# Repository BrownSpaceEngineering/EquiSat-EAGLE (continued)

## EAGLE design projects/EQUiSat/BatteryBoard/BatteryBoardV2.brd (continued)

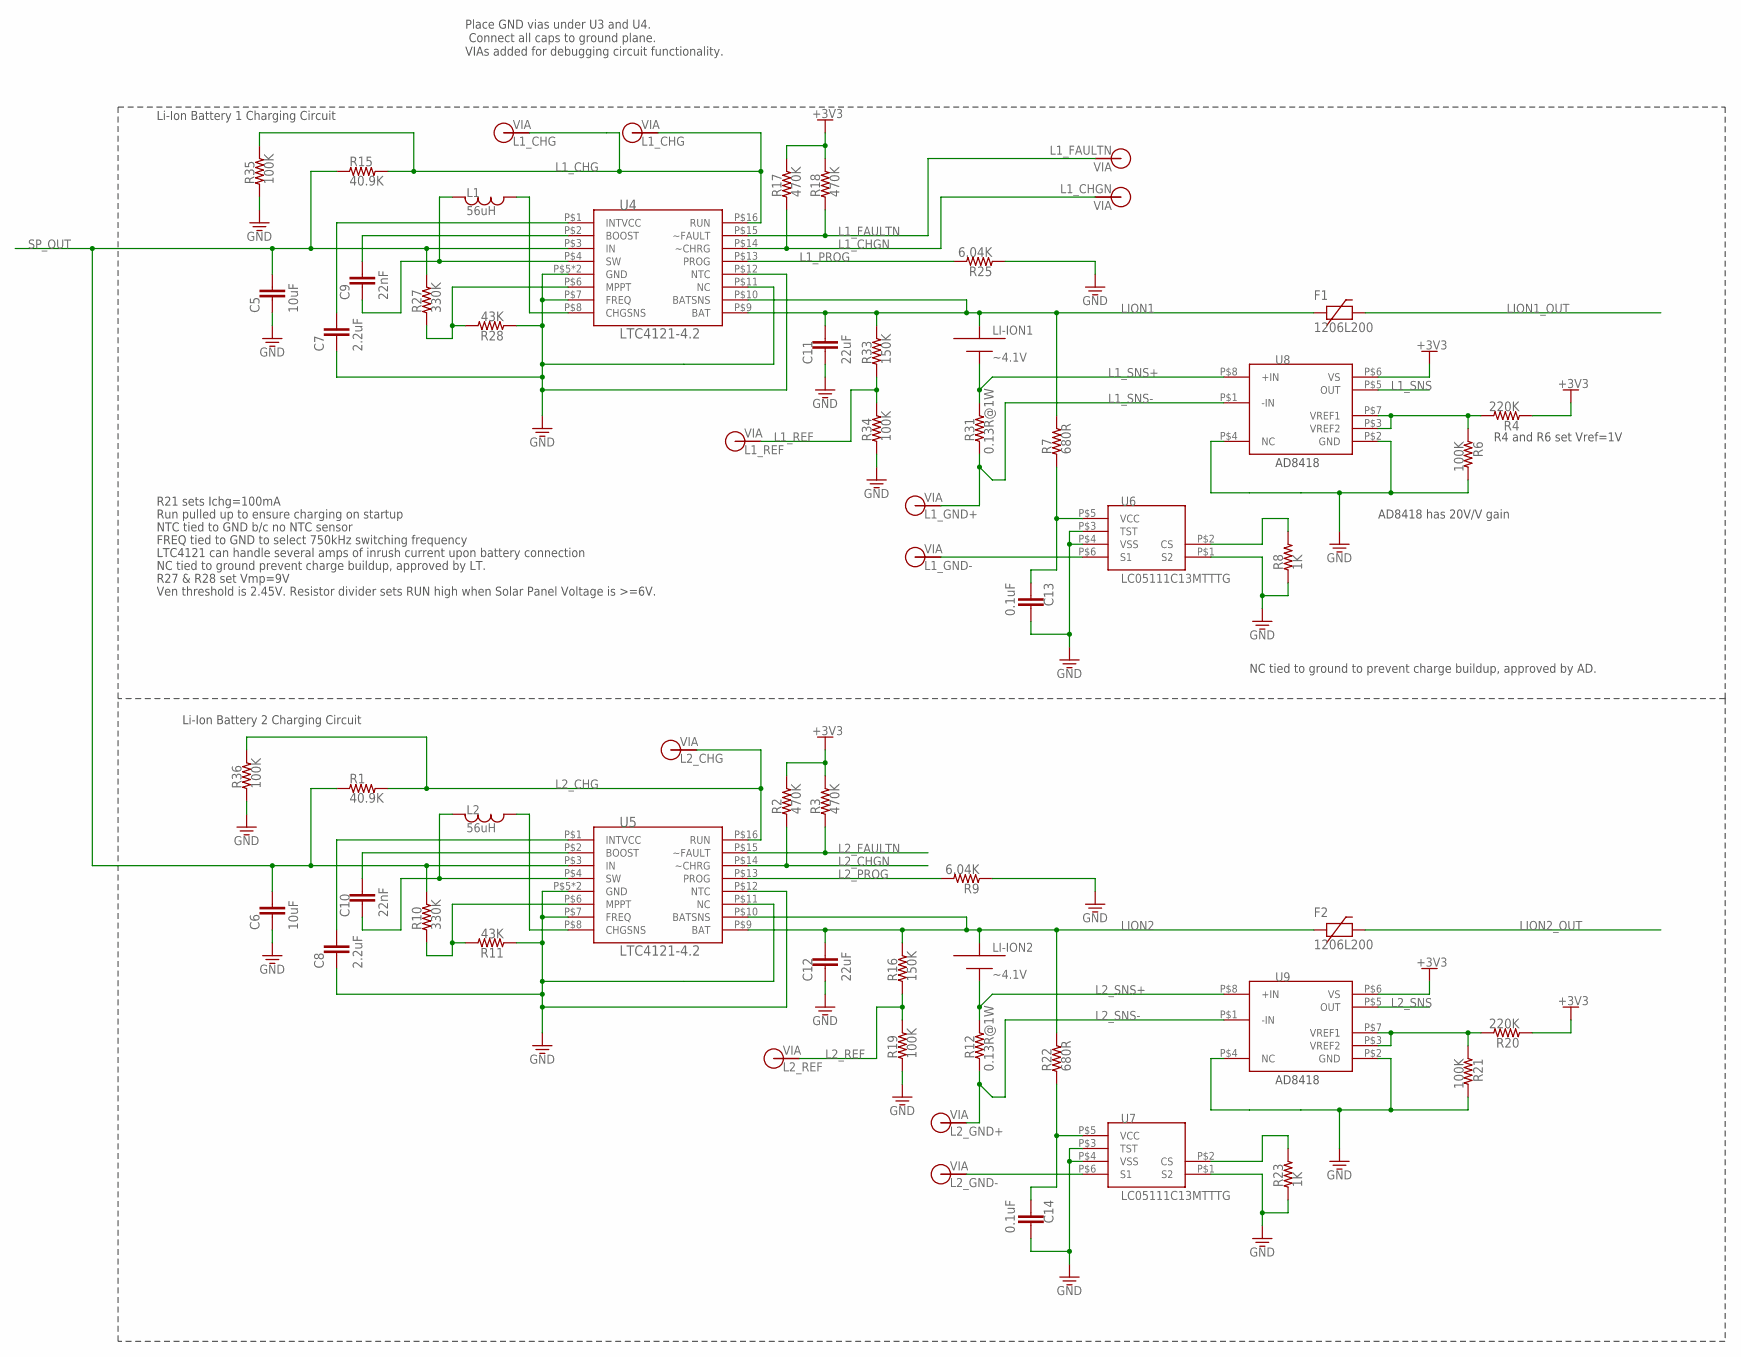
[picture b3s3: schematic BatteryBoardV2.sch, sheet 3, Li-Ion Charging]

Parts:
C5, C6: 10uF; 0805
C7, C8: 2.2uF; 0805
C9, C10: 22nF; 0805
C11, C12: 22uF; 0805
C13, C14: 0.1uF; 0805
F1, F2: 1206L200; 1206
L1, L2: 56uH; 1812
LI-ION1, LI-ION2: ~4.1V; EQUISAT-BATTERY-VA
R1, R15: 40.9K; 0805
R2, R3, R17, R18: 470K; 0805
R4, R20: 220K; 0805
R6, R19, R21, R34, R35, R36: 100K; 0805
R7, R22: 680R; 0805
R8, R23: 1K; 0805
R9, R25: 6.04K; 0805
R10, R27: 330K; 0805
R11, R28: 43K; 0805
R12, R31: 0.13R@1W; 1210
R16, R33: 150K; 0805
U4, U5: LTC4121-4.2; QFN-16-PAD
U6, U7: LC05111C13MTTTG; WDFN6
U8, U9: AD8418; MSOP-8
V20: L1_CHG; VIA-60MIL
V21: L1_REF; VIA-60MIL
V22: L1_GND+; VIA-60MIL
V23: L1_GND-; VIA-60MIL
V24: L2_GND+; VIA-60MIL
V25: L2_GND-; VIA-60MIL
V26: L1_FAULTN; VIA-60MIL-SQ
V27: L1_CHGN; VIA-60MIL-SQ
V31: L2_REF; VIA-60MIL
V33: L2_CHG; VIA-60MIL
V48: L1_CHG; VIA-60MIL-SQ

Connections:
+3V3: R2.2, R3.2, R4.1, R17.2, R18.2, R20.1, U8.P$6 (VS), U9.P$6 (VS); also elsewhere on the board
GND: C5.2, C6.2, C7.2, C8.2, C11.2, C12.2, C13.1, C14.1, R6.2, R8.1, R9.1, R11.1, R19.1, R21.2, R23.1, R25.1, R28.1, R34.1, R35.1, R36.1, U4.P$5 (GND), U4.P$7 (FREQ), U4.P$11 (NC), U4.P$12 (NTC), U4.P$17 (GND), U5.P$5 (GND), U5.P$7 (FREQ), U5.P$11 (NC), U5.P$12 (NTC), U5.P$17 (GND), U6.P$1 (S2), U6.P$3 (TST), U6.P$4 (VSS), U7.P$1 (S2), U7.P$3 (TST), U7.P$4 (VSS), U8.P$2 (GND), U8.P$4 (NC), U9.P$2 (GND), U9.P$4 (NC); also elsewhere on the board
L1_CHG: R15.2, R35.2, U4.P$16 (RUN), V20.P$1, V48.P$1
L1_CHGN: R17.1, U4.P$14 (~CHRG), V27.P$1; also elsewhere on the board
L1_FAULTN: R18.1, U4.P$15 (~FAULT), V26.P$1; also elsewhere on the board
L1_PROG: R25.2, U4.P$13 (PROG)
L1_REF: R33.1, R34.2, V21.P$1
L1_SNS: U8.P$5 (OUT); also elsewhere on the board
L1_SNS+: LI-ION1.MINUS, R31.P$2 (2), U8.P$8 (+IN)
L1_SNS-: R31.P$1 (1), U8.P$1 (-IN), V22.P$1
L2_CHG: R1.2, R36.2, U5.P$16 (RUN), V33.P$1
L2_CHGN: R2.1, U5.P$14 (~CHRG); also elsewhere on the board
L2_FAULTN: R3.1, U5.P$15 (~FAULT); also elsewhere on the board
L2_PROG: R9.2, U5.P$13 (PROG)
L2_REF: R16.1, R19.2, V31.P$1
L2_SNS: U9.P$5 (OUT); also elsewhere on the board
L2_SNS+: LI-ION2.MINUS, R12.P$2 (2), U9.P$8 (+IN)
L2_SNS-: R12.P$1 (1), U9.P$1 (-IN), V24.P$1
LION1: C11.1, F1.1, LI-ION1.PLUS, R7.2, R33.2, U4.P$9 (BAT), U4.P$10 (BATSNS)
LION1_OUT: F1.2; also elsewhere on the board
LION2: C12.1, F2.1, LI-ION2.PLUS, R16.2, R22.2, U5.P$9 (BAT), U5.P$10 (BATSNS)
LION2_OUT: F2.2; also elsewhere on the board
unnamed: C10.2, L2.P$1, U5.P$4 (SW)
unnamed: C9.2, L1.P$1, U4.P$4 (SW)
unnamed: C9.1, U4.P$2 (BOOST)
unnamed: C7.1, U4.P$1 (INTVCC)
unnamed: C10.1, U5.P$2 (BOOST)
unnamed: U6.P$6 (S1), V23.P$1
unnamed: C8.1, U5.P$1 (INTVCC)
unnamed: L1.P$2, U4.P$8 (CHGSNS)
unnamed: R27.1, R28.2, U4.P$6 (MPPT)
unnamed: R4.2, R6.1, U8.P$3 (VREF2), U8.P$7 (VREF1)
unnamed: C13.2, R7.1, U6.P$5 (VCC)
unnamed: R8.2, U6.P$2 (CS)
unnamed: R10.1, R11.2, U5.P$6 (MPPT)
unnamed: L2.P$2, U5.P$8 (CHGSNS)
unnamed: R20.2, R21.1, U9.P$3 (VREF2), U9.P$7 (VREF1)
unnamed: U7.P$6 (S1), V25.P$1
unnamed: R23.2, U7.P$2 (CS)
unnamed: C14.2, R22.1, U7.P$5 (VCC)
SP_OUT: C5.1, C6.1, R1.1, R10.2, R15.1, R27.2, U4.P$3 (IN), U5.P$3 (IN); also elsewhere on the board

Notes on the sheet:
FREQ tied to GND to select 750kHz switching frequency
R21 sets Ichg=100mA
R27 & R28 set Vmp=9V
Place GND vias under U3 and U4. Connect all caps to ground plane. VIAs added for debugging circuit functionality.
Li-Ion Battery 1 Charging Circuit
Li-Ion Battery 2 Charging Circuit
Run pulled up to ensure charging on startup
NTC tied to GND b/c no NTC sensor
LTC4121 can handle several amps of inrush current upon battery connection
NC tied to ground prevent charge buildup, approved by LT.
R4 and R6 set Vref=1V
NC tied to ground to prevent charge buildup, approved by AD.
AD8418 has 20V/V gain
Ven threshold is 2.45V. Resistor divider sets RUN high when Solar Panel Voltage is >=6V.

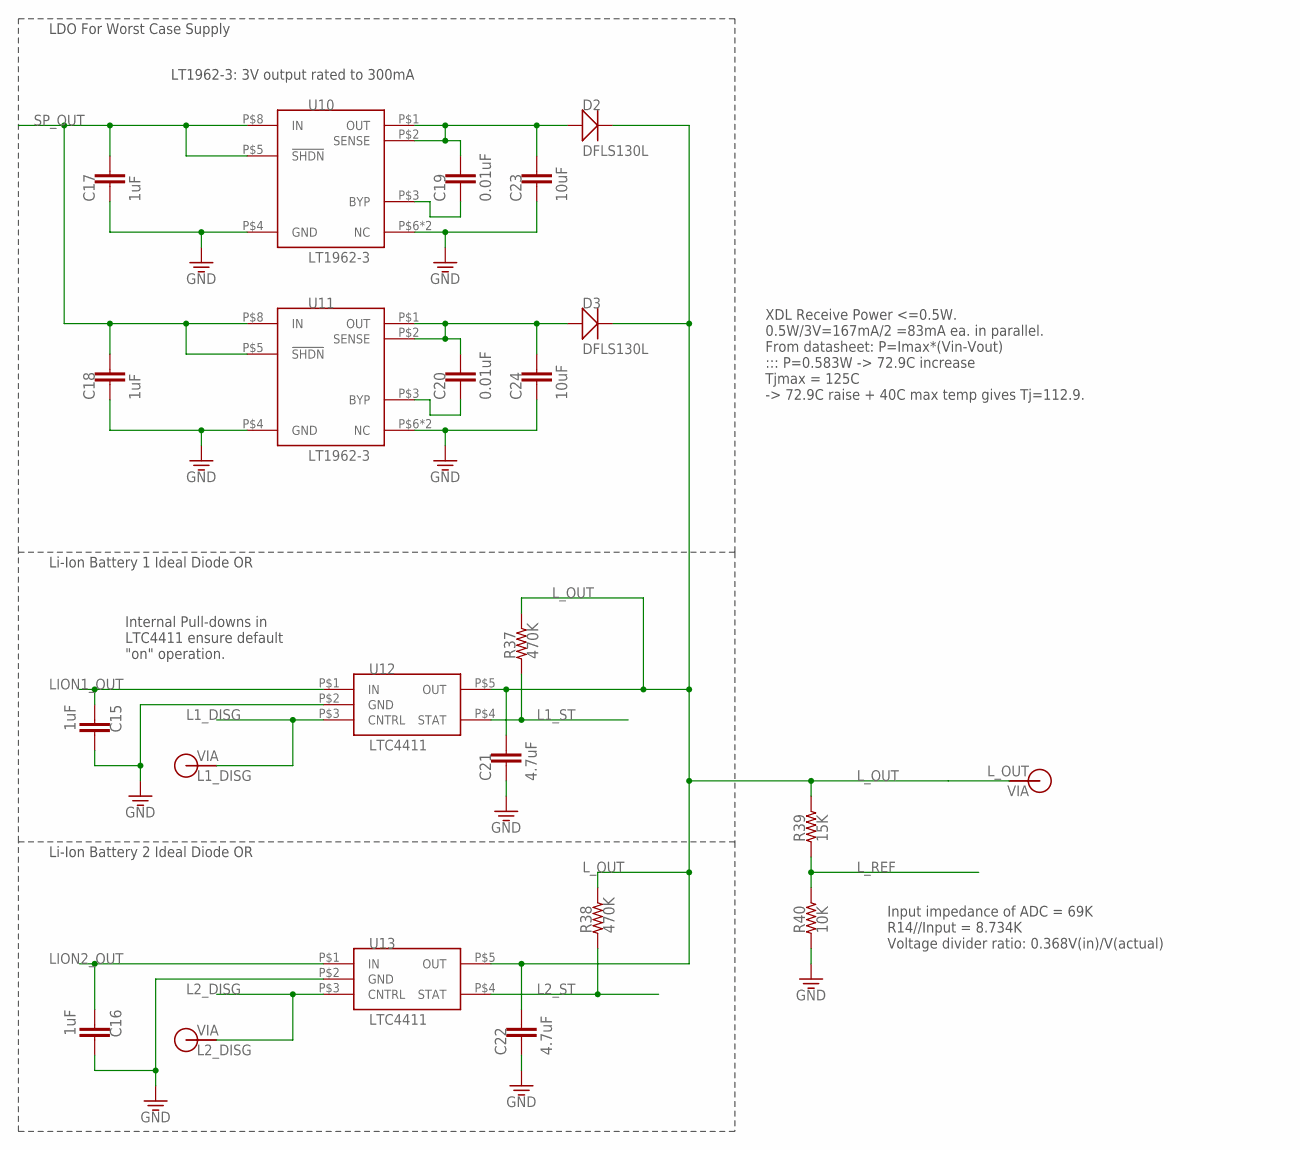
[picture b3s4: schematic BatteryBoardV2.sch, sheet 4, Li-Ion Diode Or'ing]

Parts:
C15, C16, C17, C18: 1uF; 0805
C19, C20: 0.01uF; 0805
C21, C22: 4.7uF; 0805
C23, C24: 10uF; 0805
D2, D3: DFLS130L; PWRDI-123
R37, R38: 470K; 0805
R39: 15K; 0805
R40: 10K; 0805
U10, U11: LT1962-3; MSOP-8
U12, U13: LTC4411; TSOT23-5
V29: L1_DISG; VIA-60MIL
V30: L2_DISG; VIA-60MIL
V34: L_OUT; VIA-120MIL

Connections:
GND: C15.1, C16.1, C17.2, C18.2, C21.2, C22.2, C23.2, C24.2, R40.1, U10.P$4 (GND), U10.P$6 (NC), U10.P$7 (NC), U11.P$4 (GND), U11.P$6 (NC), U11.P$7 (NC), U12.P$2 (GND), U13.P$2 (GND); also elsewhere on the board
L1_DISG: U12.P$3 (CNTRL), V29.P$1
L1_ST: R37.1, U12.P$4 (STAT); also elsewhere on the board
L2_DISG: U13.P$3 (CNTRL), V30.P$1
L2_ST: R38.1, U13.P$4 (STAT); also elsewhere on the board
LION1_OUT: C15.2, U12.P$1 (IN); also elsewhere on the board
LION2_OUT: C16.2, U13.P$1 (IN); also elsewhere on the board
L_OUT: C21.1, C22.1, D2.C, D3.C, R37.2, R38.2, R39.2, U12.P$5 (OUT), U13.P$5 (OUT), V34.P$1
L_REF: R39.1, R40.2; also elsewhere on the board
unnamed: C20.1, C24.1, D3.A, U11.P$1 (OUT), U11.P$2 (SENSE)
unnamed: C19.1, C23.1, D2.A, U10.P$1 (OUT), U10.P$2 (SENSE)
unnamed: C20.2, U11.P$3 (BYP)
unnamed: C19.2, U10.P$3 (BYP)
SP_OUT: C17.1, C18.1, U10.P$5 (!SHDN!), U10.P$8 (IN), U11.P$5 (!SHDN!), U11.P$8 (IN); also elsewhere on the board

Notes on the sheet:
Internal Pull-downs in LTC4411 ensure default "on" operation.
Li-Ion Battery 1 Ideal Diode OR
Li-Ion Battery 2 Ideal Diode OR
LDO For Worst Case Supply
LT1962-3: 3V output rated to 300mA
XDL Receive Power <=0.5W. 0.5W/3V=167mA/2 =83mA ea. in parallel. From datasheet: P=Imax*(Vin-Vout) ::: P=0.583W -> 72.9C increase Tjmax = 125C -> 72.9C raise + 40C max temp gives Tj=112.9.
Input impedance of ADC = 69K R14//Input = 8.734K Voltage divider ratio: 0.368V(in)/V(actual)

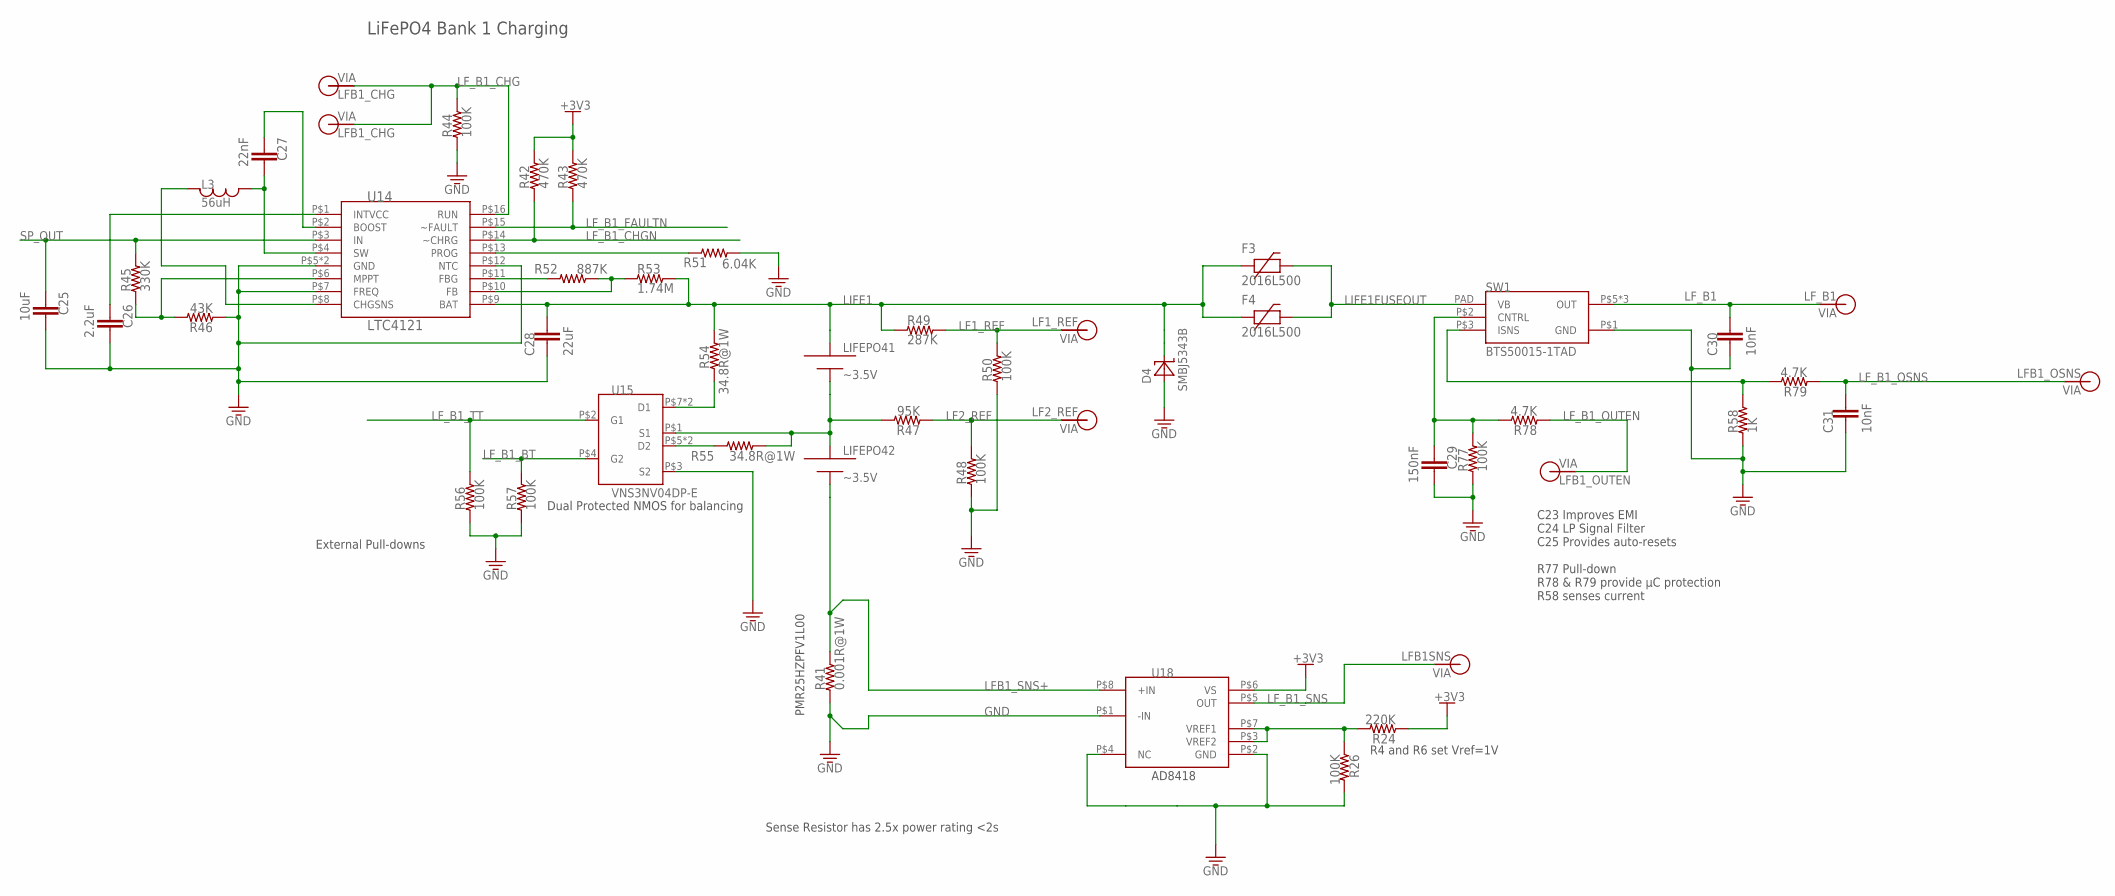
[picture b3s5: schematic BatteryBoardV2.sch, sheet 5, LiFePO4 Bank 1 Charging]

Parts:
C25: 10uF; 0805
C26: 2.2uF; 0805
C27: 22nF; 0805
C28: 22uF; 0805
C29: 150nF; 0805
C30, C31: 10nF; 0805
D4: SMBJ5343B; DO214AA
F3, F4: 2016L500; 2016
L3: 56uH; 1812
LIFEPO41: ~3.5V; EQUISAT-BATTERY-VA
LIFEPO42: ~3.5V; EQUISAT-BATTERY-VB
R24: 220K; 0805
R26, R44, R48, R50, R56, R57, R77: 100K; 0805
R41: 0.001R@1W; 1210
R42, R43: 470K; 0805
R45: 330K; 0805
R46: 43K; 0805
R47: 95K; 0805
R49: 287K; 0805
R51: 6.04K; 0805
R52: 887K; 0805
R53: 1.74M; 0805
R54, R55: 34.8R@1W; 1210
R58: 1K; 0805
R78, R79: 4.7K; 0805
SW1: BTS50015-1TAD; TO-263-7-8
U14: LTC4121; QFN-16-PAD
U15: VNS3NV04DP-E; SO-8
U18: AD8418; MSOP-8
V32: LFB1_CHG; VIA-60MIL-SQ
V35: LFB1_CHG; VIA-60MIL
V40: LFB1SNS; VIA-60MIL
V41: LF1_REF; VIA-60MIL
V42: LF2_REF; VIA-60MIL
V43: LFB1_OUTEN; VIA-60MIL
V45: LF_B1; VIA-120MIL
V46: LFB1_OSNS; VIA-60MIL

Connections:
+3V3: R24.1, R42.2, R43.2, U18.P$6 (VS); also elsewhere on the board
GND: C25.1, C26.1, C28.2, C29.1, C30.2, C31.2, D4.A, R26.2, R41.P$1 (1), R44.1, R46.1, R48.1, R50.1, R51.2, R56.1, R57.1, R58.1, R77.1, SW1.P$1 (GND), U14.P$5 (GND), U14.P$7 (FREQ), U14.P$12 (NTC), U14.P$17 (GND), U15.P$3 (S2), U18.P$1 (-IN), U18.P$2 (GND), U18.P$4 (NC); also elsewhere on the board
LF1_REF: R49.2, R50.2, V41.P$1
LF2_REF: R47.1, R48.2, V42.P$1
LFB1_SNS+: LIFEPO42.MINUS, R41.P$2 (2), U18.P$8 (+IN)
LF_B1: C30.1, SW1.P$5 (OUT), SW1.P$6 (OUT), SW1.P$7 (OUT), V45.P$1
LF_B1_BT: R57.2, U15.P$4 (G2); also elsewhere on the board
LF_B1_CHG: R44.2, U14.P$16 (RUN), V32.P$1, V35.P$1
LF_B1_CHGN: R42.1, U14.P$14 (~CHRG); also elsewhere on the board
LF_B1_FAULTN: R43.1, U14.P$15 (~FAULT); also elsewhere on the board
LF_B1_OSNS: C31.1, R79.1, V46.P$1
LF_B1_OUTEN: R78.1, V43.P$1
LF_B1_SNS: U18.P$5 (OUT), V40.P$1
LF_B1_TT: R56.2, U15.P$2 (G1); also elsewhere on the board
LIFE1: C28.1, D4.C, F3.P$1, F4.P$1, LIFEPO41.PLUS, R49.1, R53.2, R54.P$2 (2), U14.P$9 (BAT)
LIFE1FUSEOUT: F3.P$2, F4.P$2, SW1.PAD (VB)
LIFE2: LIFEPO41.MINUS, LIFEPO42.PLUS, R47.2, R55.P$1 (1), U15.P$1 (S1)
unnamed: R51.1, U14.P$13 (PROG)
unnamed: R24.2, R26.1, U18.P$3 (VREF2), U18.P$7 (VREF1)
unnamed: R54.P$1 (1), U15.P$7 (D1), U15.P$8 (D1)
unnamed: R55.P$2 (2), U15.P$5 (D2), U15.P$6 (D2)
unnamed: R52.1, U14.P$11 (FBG)
unnamed: R45.1, R46.2, U14.P$6 (MPPT)
unnamed: R52.2, R53.1, U14.P$10 (FB)
unnamed: C26.2, U14.P$1 (INTVCC)
unnamed: C27.1, L3.P$2, U14.P$4 (SW)
unnamed: C27.2, U14.P$2 (BOOST)
unnamed: L3.P$1, U14.P$8 (CHGSNS)
unnamed: C29.2, R77.2, R78.2, SW1.P$2 (CNTRL)
unnamed: R58.2, R79.2, SW1.P$3 (ISNS)
SP_OUT: C25.2, R45.2, U14.P$3 (IN); also elsewhere on the board

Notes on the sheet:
LiFePO4 Bank 1 Charging
External Pull-downs
Dual Protected NMOS for balancing
C23 Improves EMI C24 LP Signal Filter C25 Provides auto-resets R77 Pull-down R78 & R79 provide µC protection R58 senses current
R4 and R6 set Vref=1V
PMR25HZPFV1L00
Sense Resistor has 2.5x power rating <2s

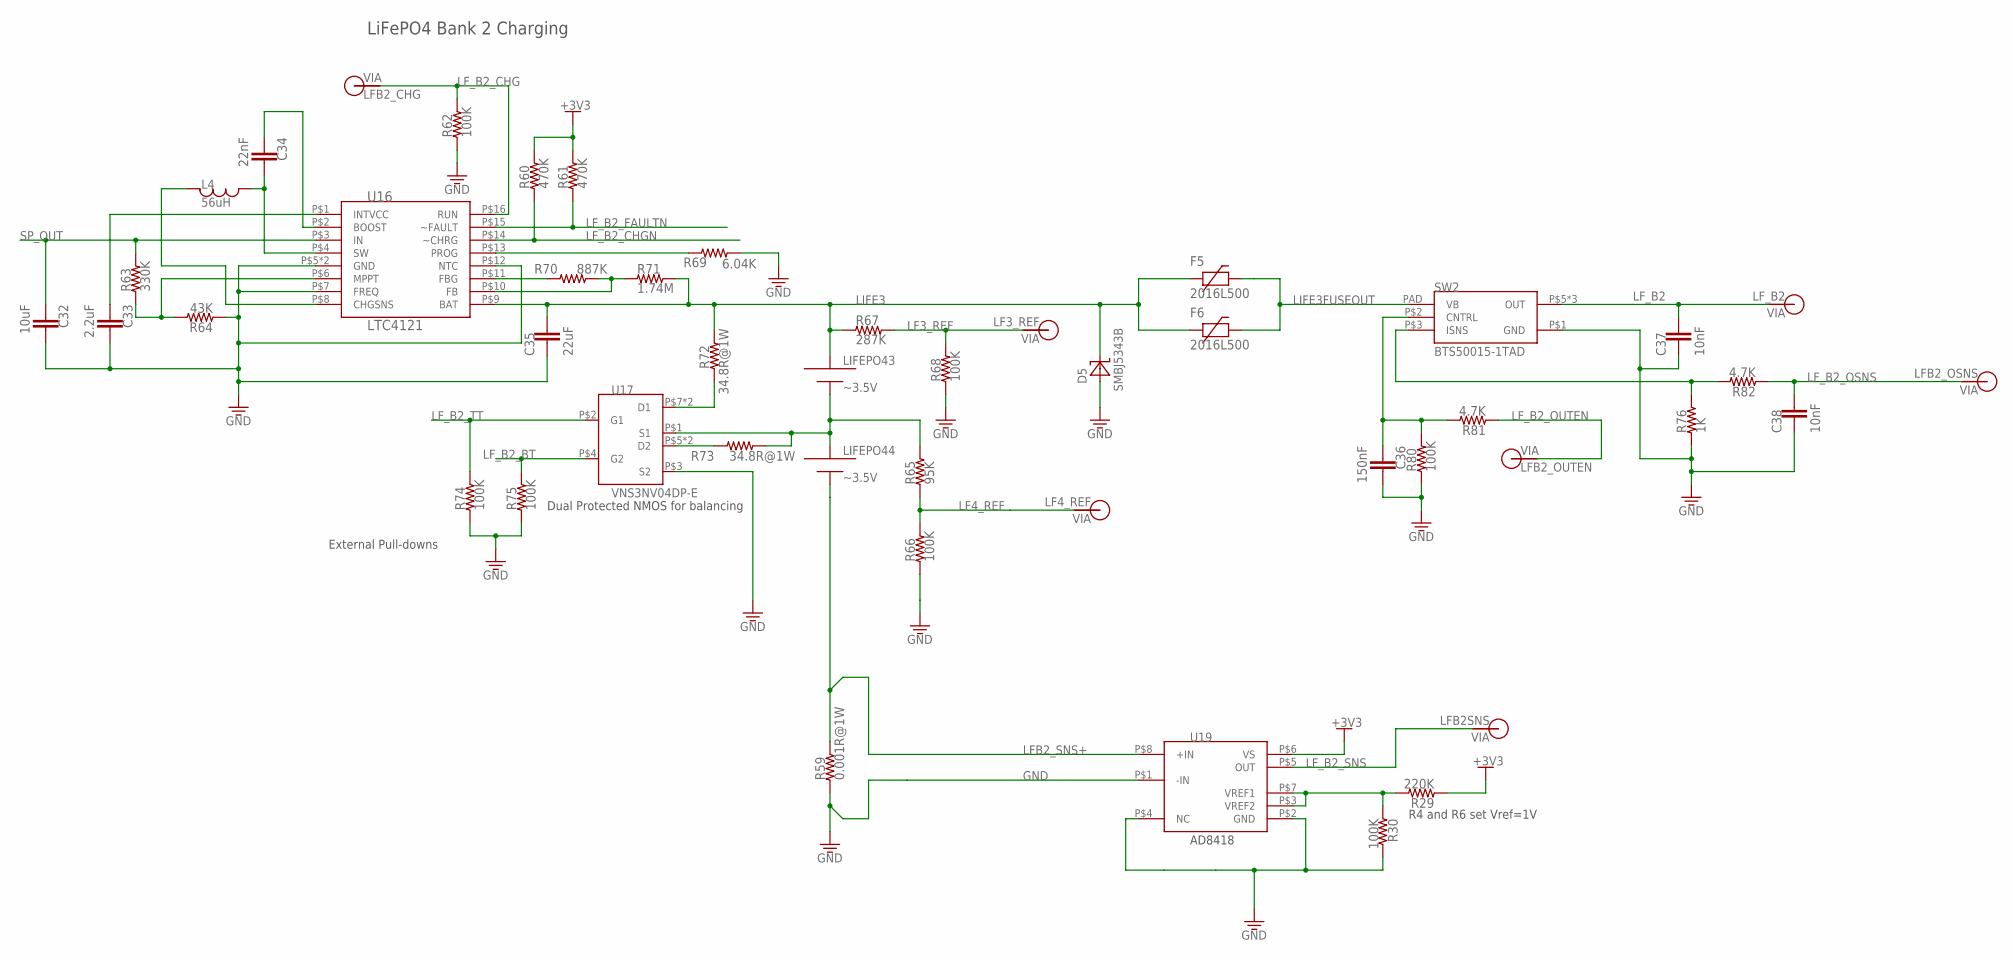
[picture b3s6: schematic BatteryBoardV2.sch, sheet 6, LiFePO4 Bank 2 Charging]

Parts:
C32: 10uF; 0805
C33: 2.2uF; 0805
C34: 22nF; 0805
C35: 22uF; 0805
C36: 150nF; 0805
C37, C38: 10nF; 0805
D5: SMBJ5343B; DO214AA
F5, F6: 2016L500; 2016
L4: 56uH; 1812
LIFEPO43: ~3.5V; EQUISAT-BATTERY-VA
LIFEPO44: ~3.5V; EQUISAT-BATTERY-VB
R29: 220K; 0805
R30, R62, R66, R68, R74, R75, R80: 100K; 0805
R59: 0.001R@1W; 1210
R60, R61: 470K; 0805
R63: 330K; 0805
R64: 43K; 0805
R65: 95K; 0805
R67: 287K; 0805
R69: 6.04K; 0805
R70: 887K; 0805
R71: 1.74M; 0805
R72, R73: 34.8R@1W; 1210
R76: 1K; 0805
R81, R82: 4.7K; 0805
SW2: BTS50015-1TAD; TO-263-7-8
U16: LTC4121; QFN-16-PAD
U17: VNS3NV04DP-E; SO-8
U19: AD8418; MSOP-8
V44: LFB2SNS; VIA-60MIL
V47: LFB2_CHG; VIA-60MIL
V49: LF3_REF; VIA-60MIL
V50: LF4_REF; VIA-60MIL
V51: LFB2_OUTEN; VIA-60MIL
V53: LF_B2; VIA-120MIL
V99: LFB2_OSNS; VIA-60MIL

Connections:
+3V3: R29.1, R60.2, R61.2, U19.P$6 (VS); also elsewhere on the board
GND: C32.1, C33.1, C35.2, C36.1, C37.2, C38.2, D5.A, R30.2, R59.P$1 (1), R62.1, R64.1, R66.1, R68.1, R69.2, R74.1, R75.1, R76.1, R80.1, SW2.P$1 (GND), U16.P$5 (GND), U16.P$7 (FREQ), U16.P$12 (NTC), U16.P$17 (GND), U17.P$3 (S2), U19.P$1 (-IN), U19.P$2 (GND), U19.P$4 (NC); also elsewhere on the board
LF3_REF: R67.2, R68.2, V49.P$1
LF4_REF: R65.1, R66.2, V50.P$1
LFB2_SNS+: LIFEPO44.MINUS, R59.P$2 (2), U19.P$8 (+IN)
LF_B2: C37.1, SW2.P$5 (OUT), SW2.P$6 (OUT), SW2.P$7 (OUT), V53.P$1
LF_B2_BT: R75.2, U17.P$4 (G2); also elsewhere on the board
LF_B2_CHG: R62.2, U16.P$16 (RUN), V47.P$1
LF_B2_CHGN: R60.1, U16.P$14 (~CHRG); also elsewhere on the board
LF_B2_FAULTN: R61.1, U16.P$15 (~FAULT); also elsewhere on the board
LF_B2_OSNS: C38.1, R82.1, V99.P$1
LF_B2_OUTEN: R81.1, V51.P$1
LF_B2_SNS: U19.P$5 (OUT), V44.P$1
LF_B2_TT: R74.2, U17.P$2 (G1); also elsewhere on the board
LIFE3: C35.1, D5.C, F5.P$1, F6.P$1, LIFEPO43.PLUS, R67.1, R71.2, R72.P$2 (2), U16.P$9 (BAT)
LIFE3FUSEOUT: F5.P$2, F6.P$2, SW2.PAD (VB)
LIFE4: LIFEPO43.MINUS, LIFEPO44.PLUS, R65.2, R73.P$1 (1), U17.P$1 (S1)
unnamed: R29.2, R30.1, U19.P$3 (VREF2), U19.P$7 (VREF1)
unnamed: R63.1, R64.2, U16.P$6 (MPPT)
unnamed: R69.1, U16.P$13 (PROG)
unnamed: R70.1, U16.P$11 (FBG)
unnamed: R70.2, R71.1, U16.P$10 (FB)
unnamed: C33.2, U16.P$1 (INTVCC)
unnamed: C34.1, L4.P$2, U16.P$4 (SW)
unnamed: C34.2, U16.P$2 (BOOST)
unnamed: L4.P$1, U16.P$8 (CHGSNS)
unnamed: R72.P$1 (1), U17.P$7 (D1), U17.P$8 (D1)
unnamed: R73.P$2 (2), U17.P$5 (D2), U17.P$6 (D2)
unnamed: R76.2, R82.2, SW2.P$3 (ISNS)
unnamed: C36.2, R80.2, R81.2, SW2.P$2 (CNTRL)
SP_OUT: C32.2, R63.2, U16.P$3 (IN); also elsewhere on the board

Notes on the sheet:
LiFePO4 Bank 2 Charging
External Pull-downs
Dual Protected NMOS for balancing
R4 and R6 set Vref=1V

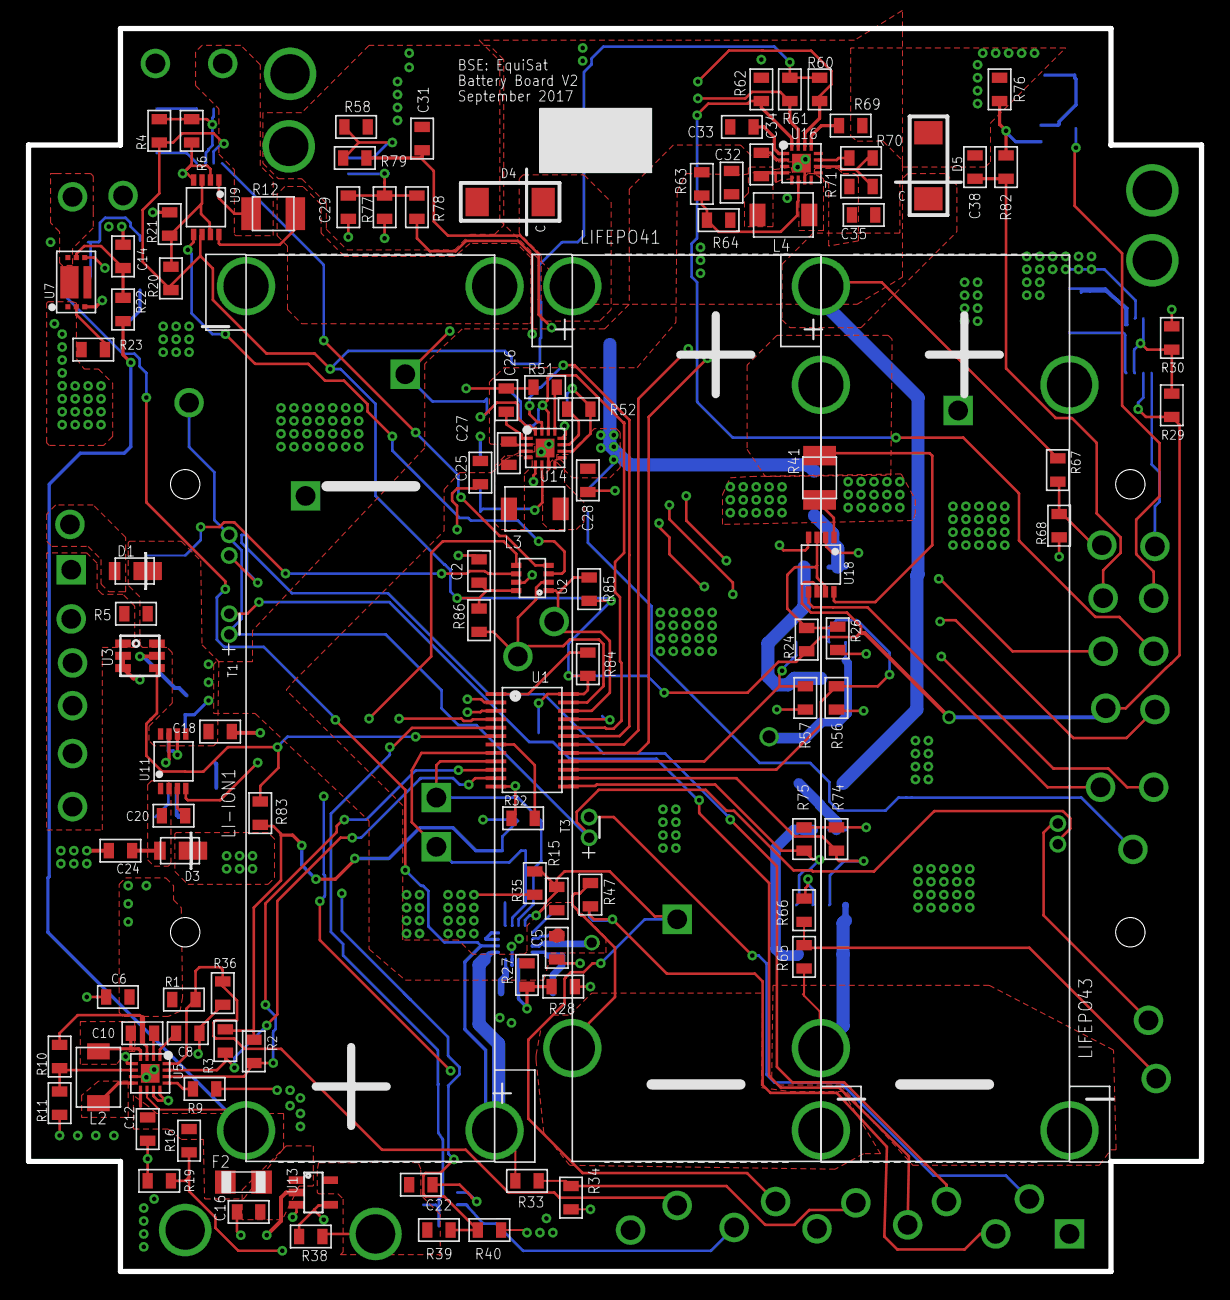
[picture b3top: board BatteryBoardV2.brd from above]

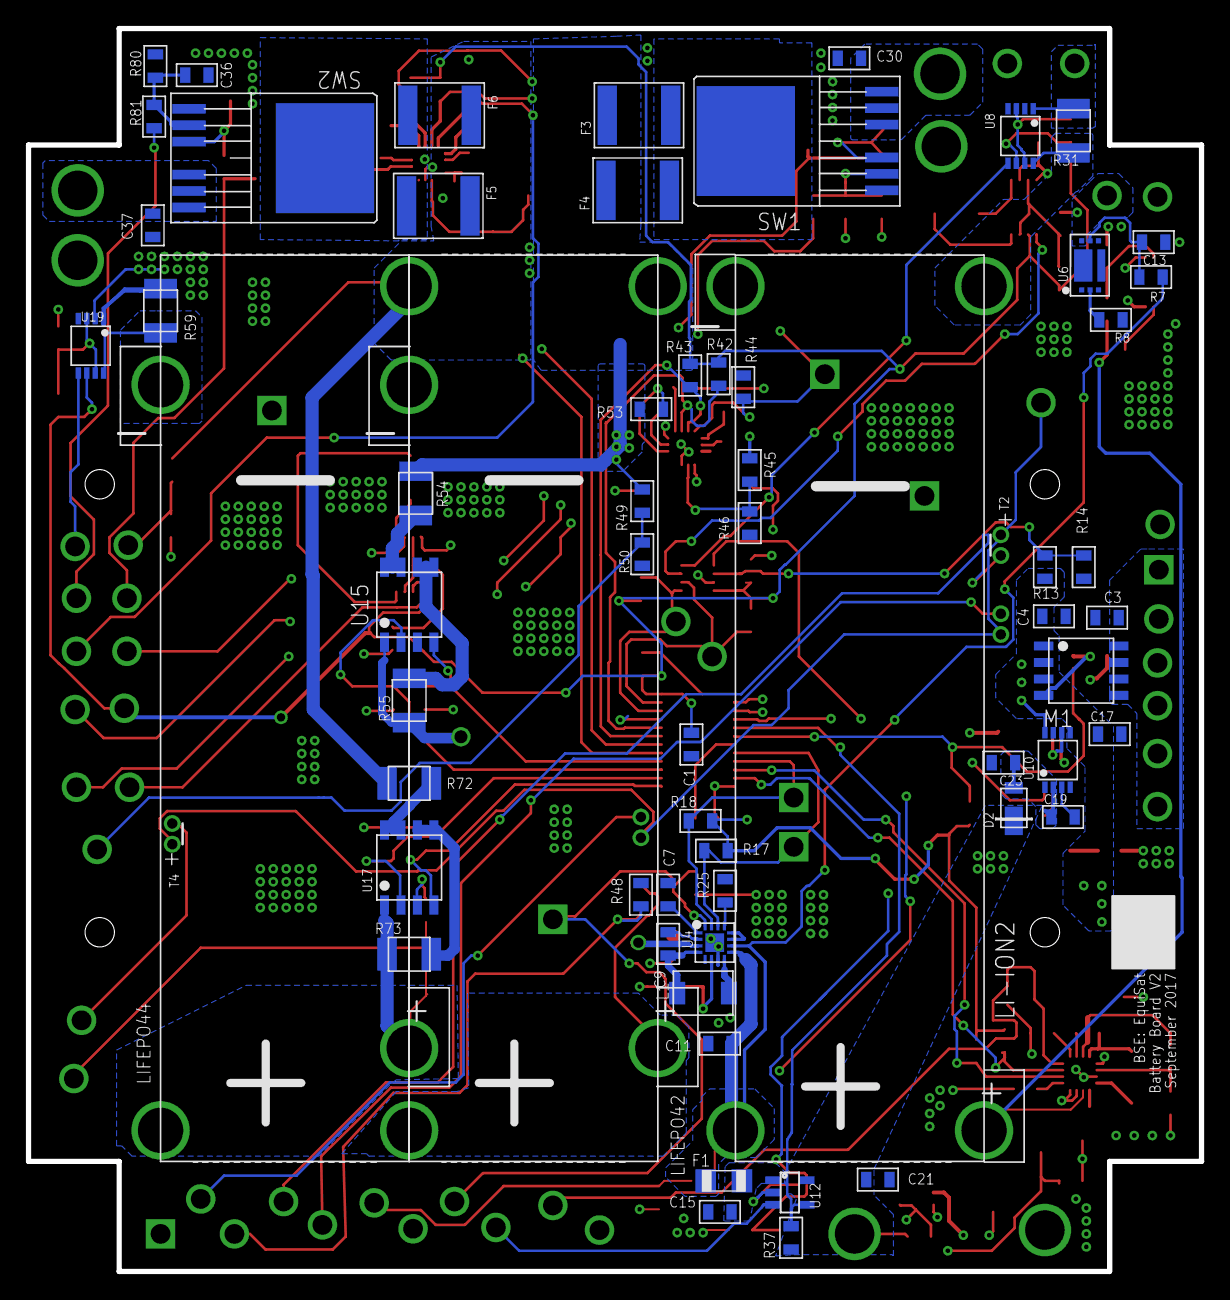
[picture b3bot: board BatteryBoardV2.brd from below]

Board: 4 copper layers, 90.6 x 96.0 mm, 225 parts (63 on the bottom side), 121 nets.

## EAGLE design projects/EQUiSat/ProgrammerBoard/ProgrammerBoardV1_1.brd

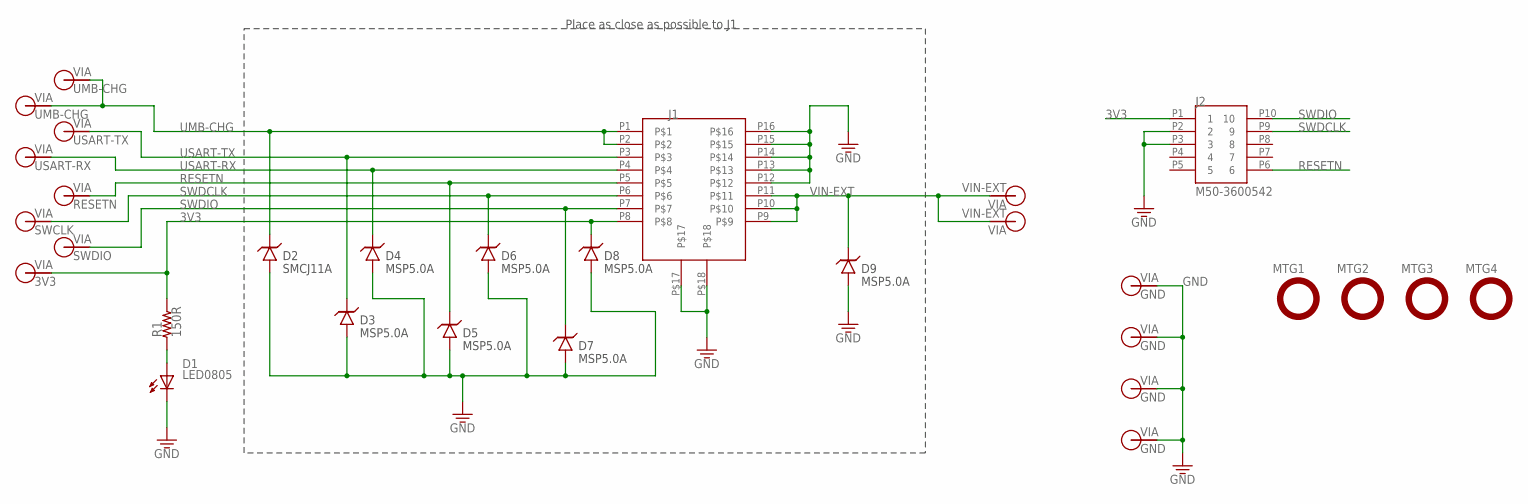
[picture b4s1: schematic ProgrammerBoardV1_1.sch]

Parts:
D1: LED0805; 0805-D
D2: SMCJ11A; DO-214AB
D3, D4, D5, D6, D7, D8, D9: MSP5.0A; MICROSMP
J1: FFC-16REVERSE; 68611614422-REVERSE
J2: M50-3600542; 10PINMALE
MTG1, MTG2, MTG3, MTG4: MTG-NPTH-M2; M2-NPTH
R1: 150R; 0805
V1, V2, V3, V4: GND; VIA-60MIL
V5: SWDIO; VIA-60MIL
V6, V7: UMB-CHG; VIA-60MIL
V8: RESETN; VIA-60MIL
V9: SWCLK; VIA-60MIL
V10: 3V3; VIA-60MIL
V11, V12: VIN-EXT; VIA-60MIL
V13: USART-RX; VIA-60MIL
V14: USART-TX; VIA-60MIL

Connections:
3V3: D8.C, J1.P8, J2.P1 (1), R1.2, V10.P$1
GND: D1.C, D2.A, D3.A, D4.A, D5.A, D6.A, D7.A, D8.A, D9.A, J1.P12, J1.P13, J1.P14, J1.P15, J1.P16, J1.P$17, J1.P$18, J2.P2 (2), J2.P3 (3), V1.P$1, V2.P$1, V3.P$1, V4.P$1
unnamed: D1.A, R1.1
RESETN: D5.C, J1.P5, J2.P6 (6), V8.P$1
SWDCLK: D6.C, J1.P6, J2.P9 (9), V9.P$1
SWDIO: D7.C, J1.P7, J2.P10 (10), V5.P$1
UMB-CHG: D2.C, J1.P1, J1.P2, V6.P$1, V7.P$1
USART-RX: D4.C, J1.P4, V13.P$1
USART-TX: D3.C, J1.P3, V14.P$1
VIN-EXT: D9.C, J1.P9, J1.P10, J1.P11, V11.P$1, V12.P$1

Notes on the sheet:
Place as close as possible to J1

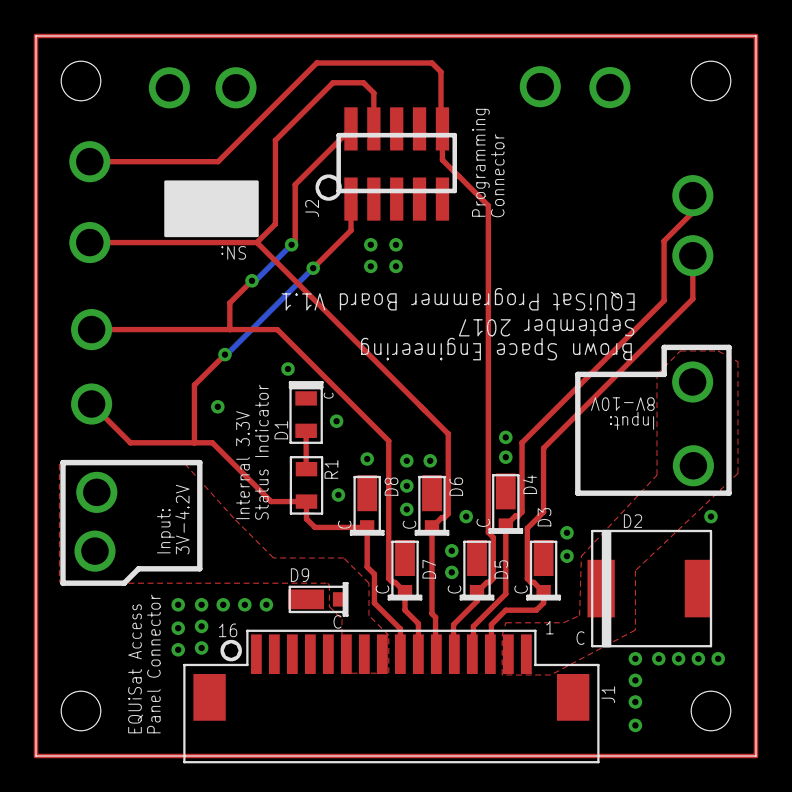
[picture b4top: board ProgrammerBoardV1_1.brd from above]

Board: 2 copper layers, 40.0 x 40.0 mm, 30 parts (0 on the bottom side), 10 nets.

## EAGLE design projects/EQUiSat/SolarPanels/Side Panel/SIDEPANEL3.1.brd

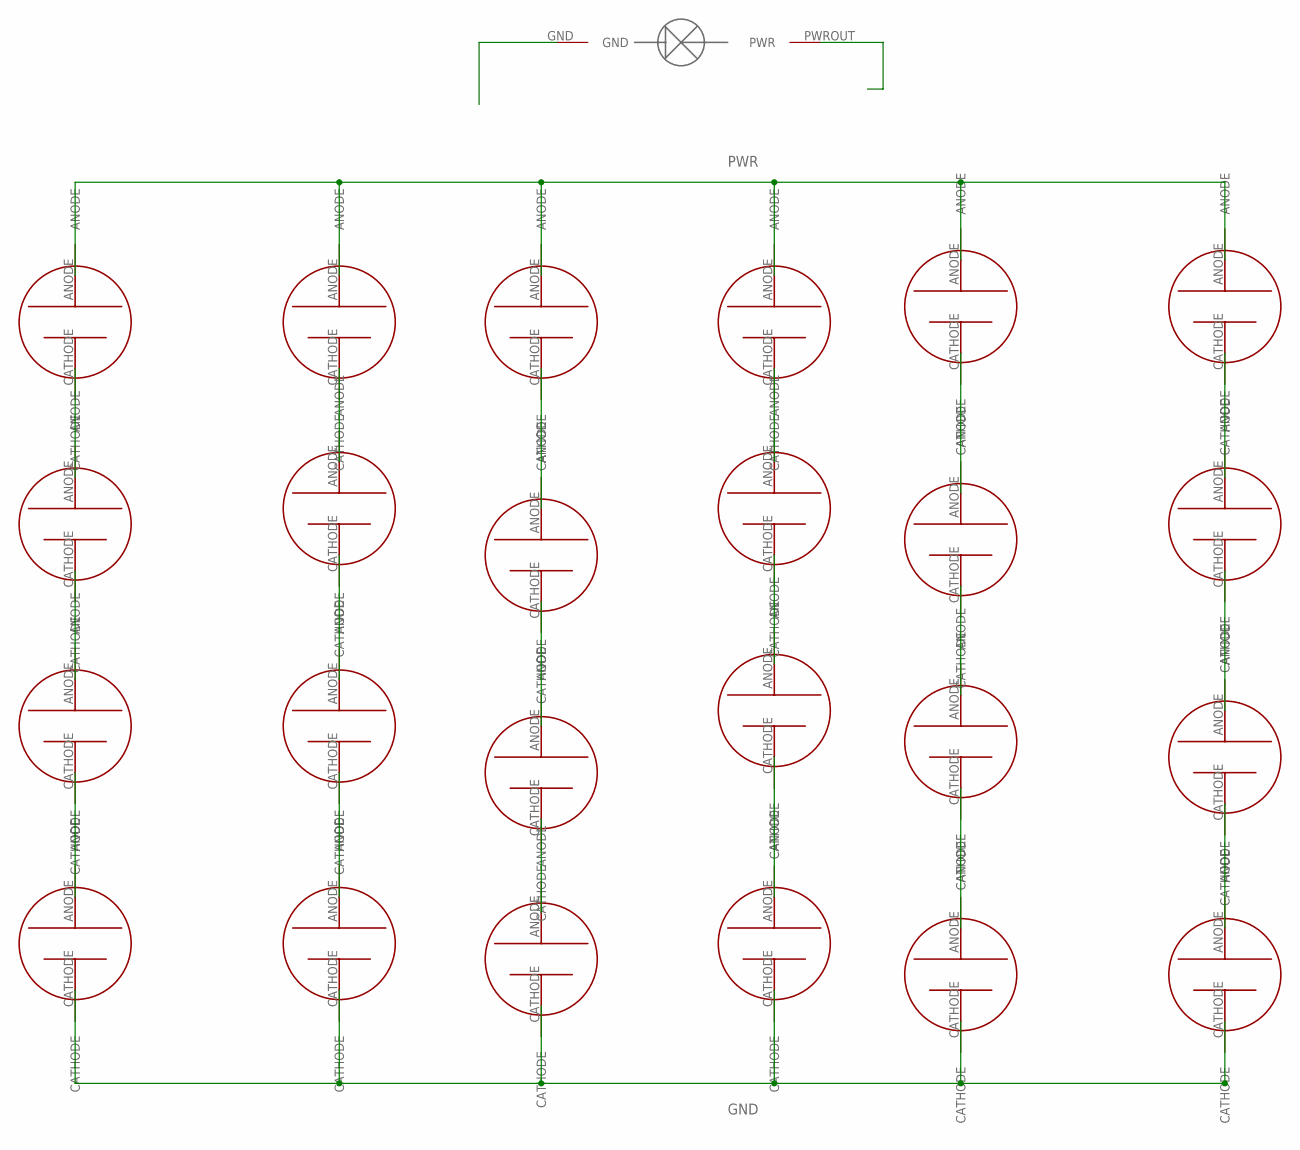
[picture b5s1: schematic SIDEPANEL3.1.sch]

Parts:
1A, 1B, 1C, 1D, 1F, 1G, 2A, 2B, 2C, 2D, 2F, 2G, 3A, 3B, 3C, 3D, 3F, 3G, 4A, 4B, 4C, 4D, 4F, 4G: NEWSOLARPANEL; SOLARCELL2
U$1: PHOTODETECTOR; PHOTODECTORDEVICE2

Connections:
GND: 4A.CATHODE, 4B.CATHODE, 4C.CATHODE, 4D.CATHODE, 4F.CATHODE, 4G.CATHODE, U$1.GND
unnamed: 2A.CATHODE, 3A.ANODE
unnamed: 1C.CATHODE, 2C.ANODE
unnamed: 2B.CATHODE, 3B.ANODE
unnamed: 2C.CATHODE, 3C.ANODE
unnamed: 2D.CATHODE, 3D.ANODE
unnamed: 3C.CATHODE, 4C.ANODE
unnamed: 2F.CATHODE, 3F.ANODE
unnamed: 1B.CATHODE, 2B.ANODE
unnamed: 2G.CATHODE, 3G.ANODE
unnamed: 3G.CATHODE, 4G.ANODE
unnamed: 1D.CATHODE, 2D.ANODE
unnamed: 3F.CATHODE, 4F.ANODE
unnamed: 3D.CATHODE, 4D.ANODE
unnamed: 3B.CATHODE, 4B.ANODE
unnamed: 3A.CATHODE, 4A.ANODE
unnamed: 1A.CATHODE, 2A.ANODE
unnamed: 1G.CATHODE, 2G.ANODE
unnamed: 1F.CATHODE, 2F.ANODE
PDOUT: U$1.PWROUT (PWR)
PWR: 1A.ANODE, 1B.ANODE, 1C.ANODE, 1D.ANODE, 1F.ANODE, 1G.ANODE

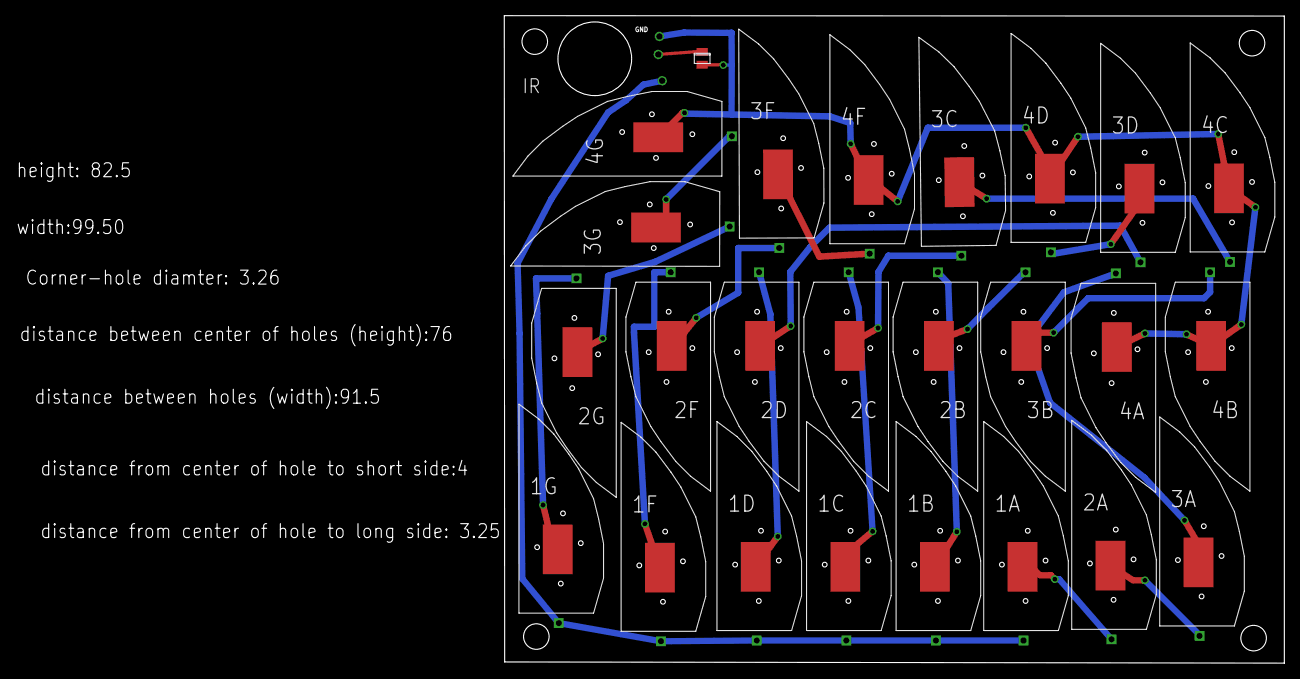
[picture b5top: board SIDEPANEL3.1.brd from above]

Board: 2 copper layers, 99.5 x 82.6 mm, 25 parts (0 on the bottom side), 20 nets.
